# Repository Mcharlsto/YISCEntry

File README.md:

# Postponed Until Further Notice
# YISCEntry
Leeds Raspberry Jam YISC Entry

PCB CAD files and Code. In EAGLE and Python.
3D print designs for enclosures in both .SKP sketchup project and .STL 3D model.

## Important Files:
* [Licence](https://github.com/Mcharlsto/YISCEntry/blob/master/DOCS/LICENSE)
* [Contributing guideline](https://github.com/Mcharlsto/YISCEntry/blob/master/DOCS/CONTRIBUTING.md)
* [Code of Conduct](https://github.com/Mcharlsto/YISCEntry/blob/master/DOCS/CODE_OF_CONDUCT.md)
* [Readme](https://github.com/Mcharlsto/YISCEntry/blob/master/README.md)
* [Wiki](https://github.com/Mcharlsto/YISCEntry/wiki)

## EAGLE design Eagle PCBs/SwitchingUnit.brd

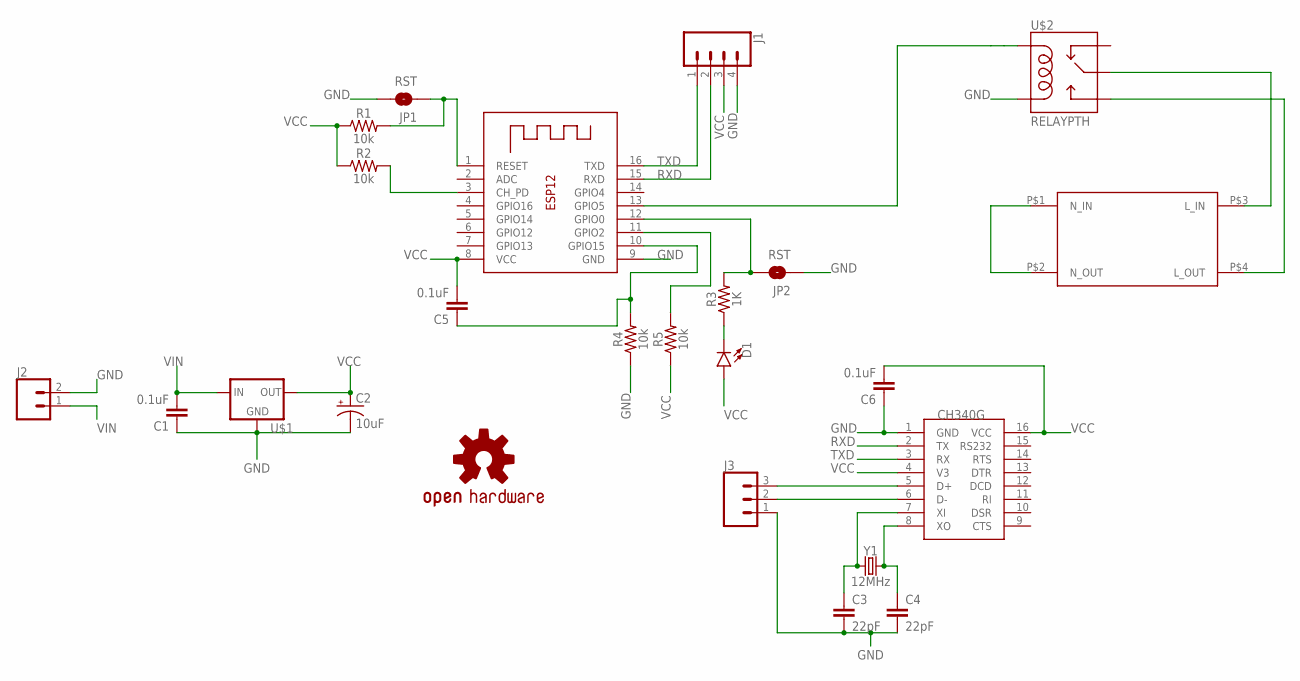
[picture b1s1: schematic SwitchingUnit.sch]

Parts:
C1, C5, C6: 0.1uF; CAP-PTH-SMALL-KIT
C2: 10uF; CPOL-RADIAL-2.5MM-5MM
C3, C4: 22pF; CAP-PTH-2.54
D1: LED5MM; LED_5MM
J1: CONN_04; 1X04
J2: CONN_02; 1X02
J3: CONN_03; 1X03
JP1, JP2: RST; SMT-JUMPER_2_NO_SILK_ROUND
LOGO1: OSHW-LOGOL; OSHW-LOGO-L
R1, R2, R4, R5: 10k; AXIAL-0.3
R3: 1K; AXIAL-0.3
U$1: V_REG_LD1117VXX; 78XXL
U$2: RELAYPTH; SRD-05VDC-SL-C
U$3: MC_MAINS; MC_MAINS_NEW
U$4: CH340G; SOIC16
X1: ESP-12
Y1: 12MHz; HC49US

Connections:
GND: C1.1, C2.2 (-), C3.2, C4.2, C6.1, J1.4, J2.2, J3.1, JP1.2, JP2.1, R4.P$1 (1), U$1.IN (GND), U$2.COIL0, U$4.1 (GND), X1.9 (GND)
unnamed: C3.1, U$4.7 (XI), Y1.1
unnamed: C4.1, U$4.8 (XO), Y1.2
unnamed: JP1.1, R1.P$2 (2), X1.1 (RESET)
unnamed: R2.P$2 (2), X1.3 (CH_PD)
unnamed: JP2.2, R3.P$2 (2), X1.12 (GPIO0)
unnamed: D1.K (C), R3.P$1 (1)
unnamed: C5.1, R4.P$2 (2), X1.10 (GPIO15)
unnamed: R5.P$2 (2), X1.11 (GPIO2)
unnamed: U$3.P$1 (N_IN), U$3.P$2 (N_OUT)
unnamed: U$2.COIL1, X1.13 (GPIO5)
unnamed: U$2.SWCOMMON, U$3.P$3 (L_IN)
unnamed: U$2.SWOPEN, U$3.P$4 (L_OUT)
unnamed: J3.3, U$4.5 (D+)
unnamed: J3.2, U$4.6 (D-)
RXD: J1.2, U$4.2 (TX), X1.15 (RXD)
TXD: J1.1, U$4.3 (RX), X1.16 (TXD)
VCC: C2.1 (+), C5.2, C6.2, D1.A, J1.3, R1.P$1 (1), R2.P$1 (1), R5.P$1 (1), U$1.GND (OUT), U$4.4 (V3), U$4.16 (VCC), X1.8 (VCC)
VIN: C1.2, J2.1, U$1.OUT (IN)

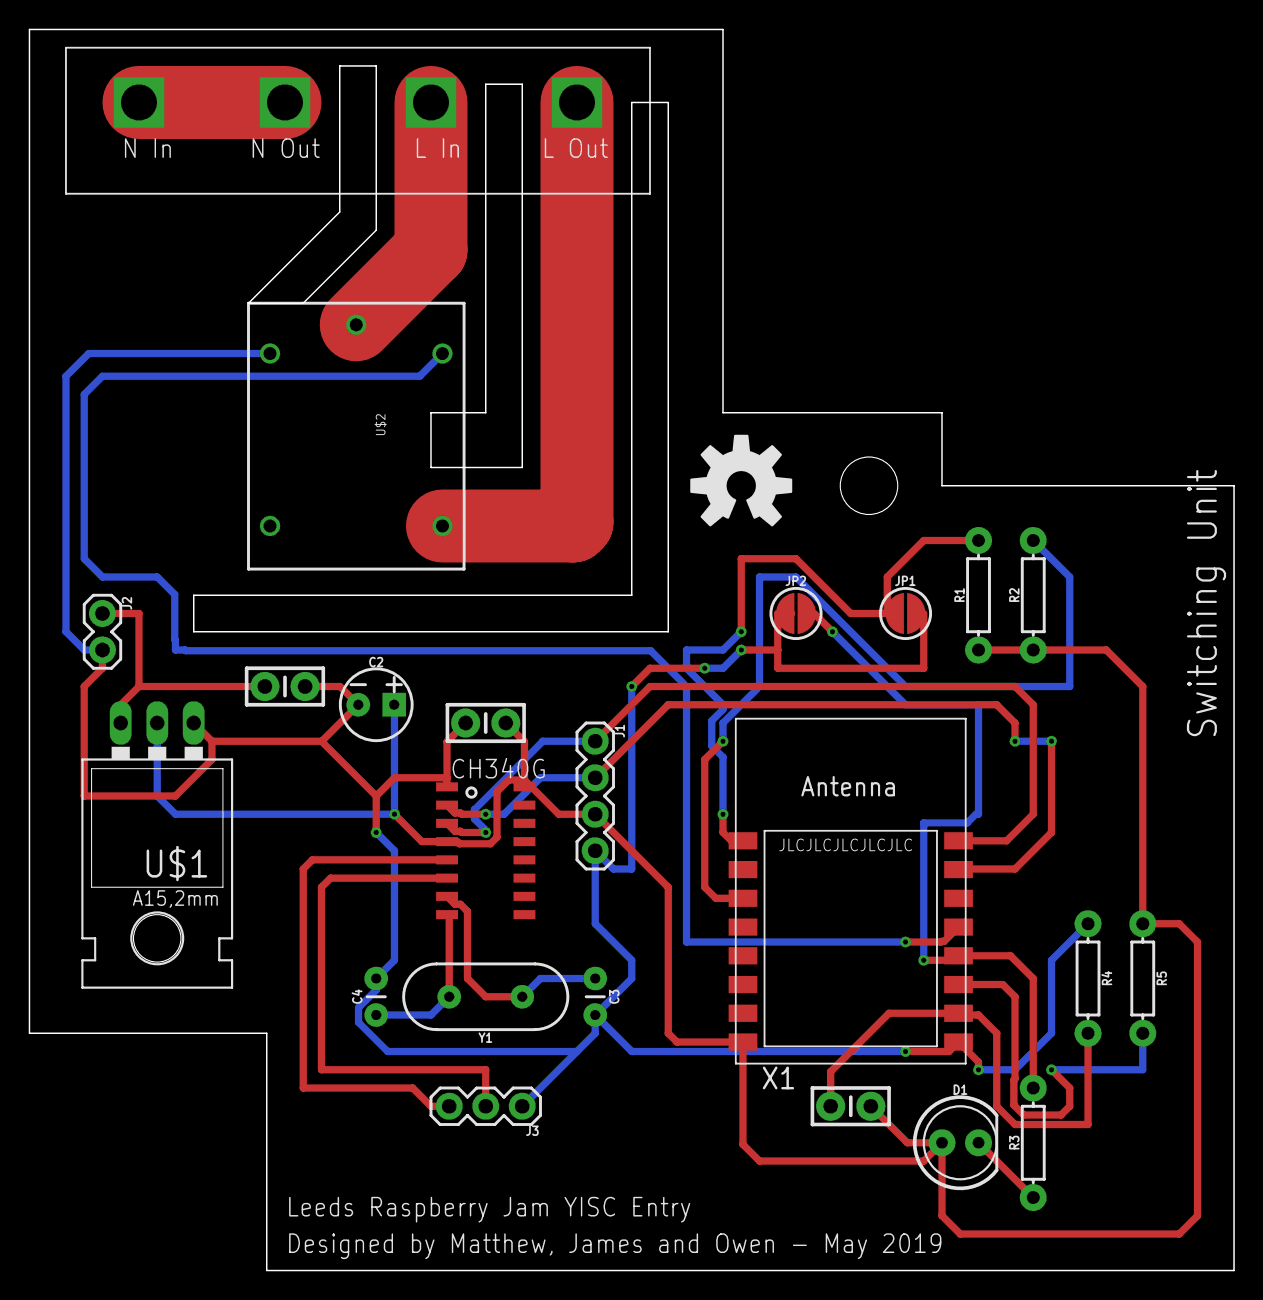
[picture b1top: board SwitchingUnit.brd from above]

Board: 2 copper layers, 83.8 x 86.4 mm, 24 parts (0 on the bottom side), 19 nets.

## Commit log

2019-06-01 Hello world!
2019-06-01 Add code folders
2019-06-01 Create LICENSE
2019-06-01 Update issue templates
2019-06-01 Update LICENSE
2019-06-01 Added BOM
    Encrypted for privacy reasons
2019-06-01 Bug fix
2019-06-02 More 3d
2019-06-02 Even more 3d
2019-06-02 Bom updates
2019-06-02 Updated 3d files and removed bom
2019-06-02 NetFabb'd the models
2019-06-02 Semi-finalised 3D Designs
2019-06-08 Fix base 1
2019-06-08 Stuiff
2019-06-08 Enlargement of holes in all files
2019-06-09 Rename CODE_OF_CONDUCT.md to DOCS/CODE_OF_CONDUCT.md
2019-06-09 Rename LICENSE to DOCS/LICENSE
2019-06-09 Rename CONTRIBUTING.md to DOCS/CONTRIBUTING.md
2019-06-09 Update README.md
    Corrected links

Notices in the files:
parts and their libraries:
SparkFun-Capacitors: Licensing: Creative Commons ShareAlike 4.0 International - https://creativecommons.org/licenses/by-sa/4.0
